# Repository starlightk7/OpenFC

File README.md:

# OpenFC

## Introduction

This repository contains OSHW Reproduction Parts related to the Famicom (FC) game console under the umbrella name OpenFC.

These parts are freely available under the terms of the [CERN-OHL-S](https://github.com/starlightk7/OpenFC/blob/main/LICENSE) license for you to use, study, modify, or sell. The source files are provided as-is with no warranty or entitlement for support to you or any users that you sell manufactured boards to. See [LICENSE](https://github.com/starlightk7/OpenFC/blob/main/LICENSE) and [NOTICE](https://github.com/starlightk7/OpenFC/blob/main/NOTICE) for details. Please carefully read these files to understand your obligations if you choose to distribute this project or modifications of it.

## Sample Build

<div></div>

## Usage

Suggested usage for the documents and boards in this repository:

* Studying the hardware and learning about it's function
* Aiding repairs and failure diagnostics through the created [schematics](https://starlightk7.github.io/OpenFC/#/schematic) and boardviews
* Repairing broken consoles via replacement, reproduction boards and tested replacement [BOMs](https://starlightk7.github.io/OpenFC/#/bom).
* Building a customized console as a DIY project, for hobby or educational purposes.

## Documentation

Please read the [documentation](https://starlightk7.github.io/OpenFC/) carefully before using the project.

You can also watch an HVC install video from [1upRestorations (English)](https://youtu.be/V8x1_Q33Uts)

## Getting a Board

The project officially distributes boards from [Japan (inexpensive international shipping available)](https://ko-fi.com/starlightk7/shop), the [US](https://1uprestorations.com/collections/console-mod-parts/) and the [UK](https://www.retroupgrades.co.uk/). If you just wish to simply obtain a board for yourself, it will often be cheaper than ordering from the fab directly.

***Support is offered to those who purchased a board from a vendor listed below. No support is provided for fabricating these files on your own. If you choose that route, you should understand what you are doing and are responsible for ensuring it is done right. I am not responsible for any defects that may arise from improperly manufacturing these files, or for defects arising from modifications made by you or your PCB fab during manufacturing. If you produce these boards for sale without becoming an authorized distributor, you are responsible for any and all customer support related to the product as well as your compliance with the project's license***. 

If you have any questions about this, feel free to contact with questions. If you are interested in becoming an authorized distributor for your region, and thus gaining support for your users, please contact me via Discord or Twitter.

The ultimate goal of this project is to eventually document and reproduce all models, but it will take quite some time. If you believe in the long term goal, consider subscribing on Ko-Fi; labor aside, donor boards to research, prototypes, and parts are all expensive, and those funds will help offset those costs to complete more boards.

Feel free to come chat with us on Discord: 

All boards in this project are ~40 years old at the time of writing. All relevant patents worldwide have long expired. This project is not affiliated with or endorsed by the big N.

## Commissions

I do not have time to build commissions on a regular basis, however, there are members of the retro community whom offer this service.

| US/Canada |
|-----------|
| [1upRestorations (United States)'](https://1uprestorations.com/) |

## Disclaimer

**WARNING:** Doing a full build is an advanced project. Please carefully read the documentation and required skills and experience before purchasing or ordering a board. Purchasing boards and parts does not guarantee that you can be successful in doing a build. Significant experience in soldering and desoldering, along with a variety of tools are necessary. Your first build will likely not work on its first boot. Patience, analysis, and debugging will likely be necessary to bring the unit online. Order at your own risk. The author provides no guarantee of your success, and also cannot guarantee that any given vendor can fabricate these boards correctly. If you are ordering boards, please consult with your target vendor before ordering if you wish to order a board.

## Parts Index

### Motherboards

| Part Number | Description | Region | Status| Japan | United States | United Kingdom |
|-------------|-------------|----------------------|-------|-------|---------------|----------------|
| HVC-CPU-01 | AV Famicom / New Famicom | NTSC-J | Need Donor  | N/A | N/A | N/A |
| HVC-CPU-02 | AV Famicom / New Famicom | NTSC-J | Need Donor  | N/A | N/A | N/A |
| HVC-CPU-03 | AV Famicom / New Famicom | NTSC-J | Planned     | N/A | N/A | N/A |
| HVC-CPU-04 | AV Famicom / New Famicom | NTSC-J | Planned     | N/A | N/A | N/A |
| HVC-CPU-05 | AV Famicom / New Famicom | NTSC-J | Planned     | N/A | N/A | N/A |
| HVC-CPU-06 | AV Famicom / New Famicom | NTSC-J | Planned     | N/A | N/A | N/A |
| HVC-CPU-07 (1984) | The most common HVC motherboard. Most often comes with Rev. E chips. | NTSC-J | Released | [Ko-Fi (Direct)](https://ko-fi.com/starlightk7/shop), [eBay (Direct)](https://www.ebay.com/usr/starlightk7), [Etsy (Direct)](https://starlightretro.etsy.com) | [1upRestorations](https://1uprestorations.com/collections/console-mod-parts) | [RetroUpgrades](https://www.retroupgrades.co.uk/product/opensfc-shvc-bundle) |
| HVC-CPU-GPM-01 | Redesign that worked on lowering EMI for VCCI compliance | NTSC-J | Planned | N/A | N/A | N/A |
| HVC-CPU-GPM-02 | Redesign that worked on lowering EMI for VCCI compliance | NTSC-J | Planned | N/A | N/A | N/A |
| HVCN-CPU-01 | AV Famicom / New Famicom | NTSC-J | Need Donor  | N/A | N/A | N/A |
| HVCN-CPU-02 | AV Famicom / New Famicom | NTSC-J | In Progress | N/A | N/A | N/A |

### Power AV

| Part Number | Description | Region | Status| Japan | United States | United Kingdom |
|-------------|-------------|----------------------|-------|-------|---------------|----------------|
| KP-782 | Early Type Original Power / RF Board | NTSC-J | Planned | N/A | N/A | N/A |
| KP-917 | Late Type Original Power / RF Board | NTSC-J | In Testing | N/A | N/A | N/A |
| OFC-PWRAV-01 | Original Design. Backport of SFC-style Power/Audio circuit w/ THS7314 for Composite Video. | NTSC-J | Released | [Ko-Fi (Direct)](https://ko-fi.com/starlightk7/shop), [eBay (Direct)](https://www.ebay.com/usr/starlightk7), [Etsy (Direct)](https://starlightretro.etsy.com) | [1upRestorations](https://1uprestorations.com/collections/console-mod-parts) | [RetroUpgrades](https://www.retroupgrades.co.uk/product/opensfc-shvc-bundle) |

### Controllers

| Part Number | Description | Region | Status| Japan | United States | United Kingdom |
|-------------|-------------|----------------------|-------|-------|---------------|----------------|
| 56.8231A | Found in Early Circle Button Controllers Pre-NES Launch | NTSC-J | Planned | N/A | N/A | N/A |
| 56.8231B | Found in Most Circle Buttton Controllers. Official NES Support | NTSC-J / NTSC-U | Released | [Ko-Fi (Direct)](https://ko-fi.com/starlightk7/shop), [eBay (Direct)](https://www.ebay.com/usr/starlightk7), [Etsy (Direct)](https://starlightretro.etsy.com) | [1upRestorations](https://1uprestorations.com/collections/console-mod-parts) | [RetroUpgrades](https://www.retroupgrades.co.uk/product/opensfc-shvc-bundle) |
| 56.8232A  | Circle Button Player 2 Controller | NTSC-J | Released | [Ko-Fi (Direct)](https://ko-fi.com/starlightk7/shop), [eBay(Direct)](https://www.ebay.com/usr/starlightk7) | [1upRestorations](https://1uprestorations.com/collections/console-mod-parts) | [RetroUpgrades](https://www.retroupgrades.co.uk/) |

### Cartridges

There are none currently in progress, but they are planned for future.

### Accessories

There are none currently in progress, but they planned for future.

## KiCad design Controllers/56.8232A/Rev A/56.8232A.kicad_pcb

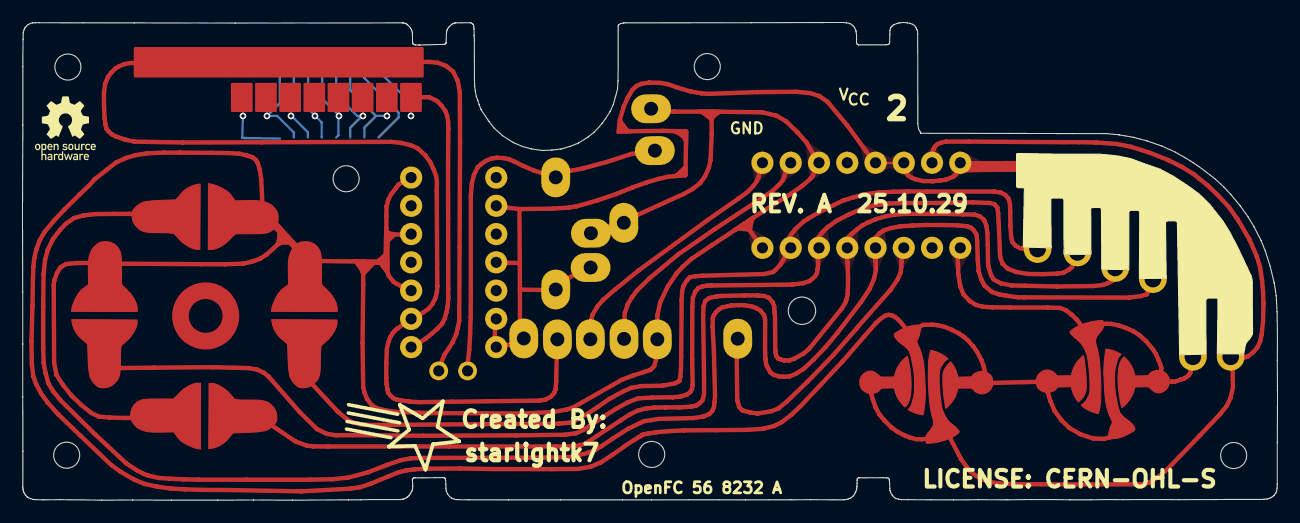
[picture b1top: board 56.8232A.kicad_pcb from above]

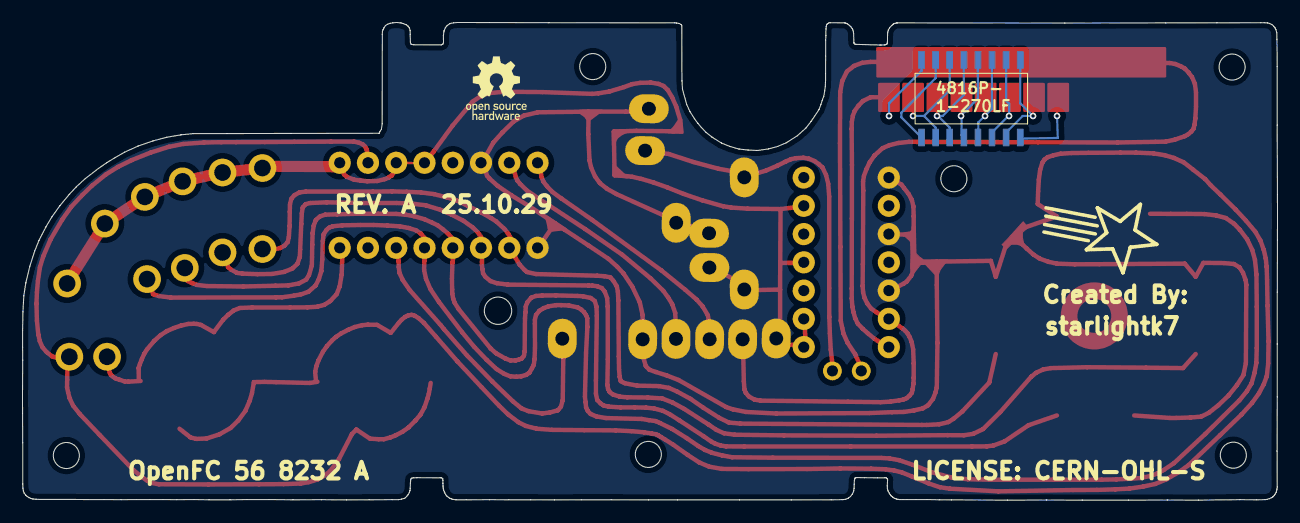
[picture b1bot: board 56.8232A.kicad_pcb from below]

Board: 2 copper layers, 113.0 x 43.0 mm, 23 parts (4 on the bottom side), 21 nets.

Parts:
C1: 0.33uf; C_THT_Small
IC1: IC4021
IC2: MIC_IC
J1, J2, J3, J4, J5, J7, J8, J9, J11, J12, J13: +5V; P1_Wire
R1: 2.2k; R_THT_Alt_Long
RN1: 40k x6; P2_CarbonTraces
RN2: 27ohm x8 SOIC; R_Array_08_SOIC16
S1: LEFT; P1_DPad
S3: UP; P1_DPad
S4: RIGHT; P1_DPad
S5: DOWN; P1_DPad
S9: B; P1_AB
S10: A; P1_AB

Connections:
GND: IC1.8 (GND), IC1.11 (GND), IC2.3 (I2), IC2.5 (I3), IC2.7 (VSS), J4.1, J8.1, J9.1, J12.1, S1.2 (Out), S3.2 (Out), S4.2 (Out), S5.2 (Out), S9.2 (Out), S10.2 (Out)
unnamed: IC1.1 (A), RN1.10, S10.1 (In)
unnamed: IC1.15 (B), RN1.12, S9.1 (In)
unnamed: IC1.10 (CLK), J3.1
unnamed: IC1.3 (Data), J13.1
unnamed: IC1.5 (Down), RN1.6, S5.1 (In)
unnamed: IC1.9 (Latch), J2.1
unnamed: IC1.6 (Left), RN1.4, S1.1 (In)
unnamed: IC1.7 (Right), RN1.2, S4.1 (In)
unnamed: IC1.4 (Up), RN1.8, S3.1 (In)
unnamed: IC2.1 (I1), RN2.16 (R1.2)
unnamed: C1.2, IC2.2 (O1), J1.1
unnamed: C1.1, J11.1, R1.1
unnamed: RN2.1 (R1.1), RN2.15 (R2.2)
unnamed: RN2.2 (R2.1), RN2.14 (R3.2)
unnamed: RN2.3 (R3.1), RN2.13 (R4.2)
unnamed: RN2.4 (R4.1), RN2.12 (R5.2)
unnamed: RN2.5 (R5.1), RN2.11 (R6.2)
unnamed: RN2.6 (R6.1), RN2.10 (R7.2)
unnamed: RN2.7 (R7.1), RN2.9 (R8.2)
VCC: IC1.13 (Start), IC1.14 (Sel.), IC1.16 (5V), IC2.9 (I4), IC2.11 (I5), IC2.13 (I6), IC2.14 (VDD), J5.1, J7.1, R1.2, RN1.1, RN1.3, RN1.5, RN1.7, RN1.9, RN1.11

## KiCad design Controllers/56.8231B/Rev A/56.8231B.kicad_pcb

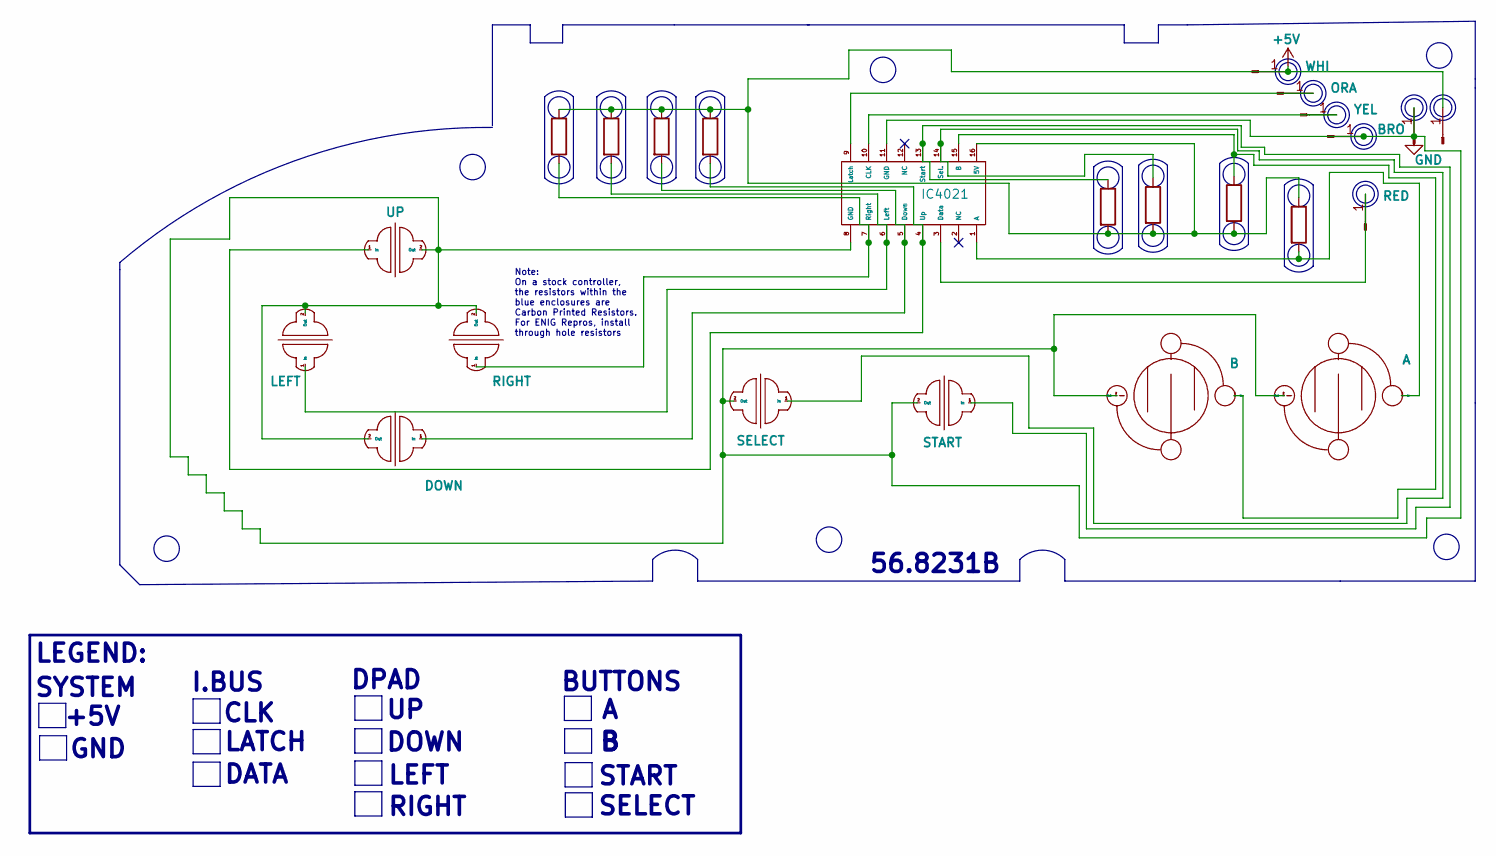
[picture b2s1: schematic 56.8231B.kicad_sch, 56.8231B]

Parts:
IC1: IC4021
J1: ORA; P1_Wire
J2: WHI; P1_Wire
J3: YEL; P1_Wire
J4: BRO; P1_Wire
J5: +5V; P1_Wire
J6: GND; P1_Wire
J7: RED; P1_Wire
R1, R2, R3, R4, R5, R6, R7, R8: R; CarbonResistor
S1: LEFT; P1_DPad
S2: SELECT; P1_SelectStart
S3: UP; P1_DPad
S4: RIGHT; P1_DPad
S5: DOWN; P1_DPad
S6: START; P1_SelectStart
S9: B; P1_AB
S10: A; P1_AB

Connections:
+5V: IC1.16 (5V), J2.1, J5.1, R1.1, R2.1, R3.1, R4.1, R5.2, R6.2, R7.2, R8.1
GND: IC1.8 (GND), IC1.11 (GND), J4.1, J6.1, S1.2 (Out), S2.2 (Out), S3.2 (Out), S4.2 (Out), S5.2 (Out), S6.2 (Out), S9.2 (Out), S10.2 (Out)
unnamed: IC1.1 (A), R8.2, S10.1 (In)
unnamed: IC1.15 (B), R7.1, S9.1 (In)
unnamed: IC1.10 (CLK), J3.1
unnamed: IC1.3 (Data), J7.1
unnamed: IC1.5 (Down), R3.2, S5.1 (In)
unnamed: IC1.9 (Latch), J1.1
unnamed: IC1.6 (Left), R2.2, S1.1 (In)
unnamed: IC1.7 (Right), R1.2, S4.1 (In)
unnamed: IC1.14 (Sel.), R6.1, S2.1 (In)
unnamed: IC1.13 (Start), R5.1, S6.1 (In)
unnamed: IC1.4 (Up), R4.2, S3.1 (In)

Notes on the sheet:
BUTTONS
START
LEFT
DOWN
Note: On a stock controller, the resistors within the blue enclosures are Carbon Printed Resistors. For ENIG Repros, install through hole resistors
DATA
56.8231B
LATCH
SELECT
DPAD
LEGEND:
+5V
SYSTEM
CLK
GND
RIGHT
I.BUS

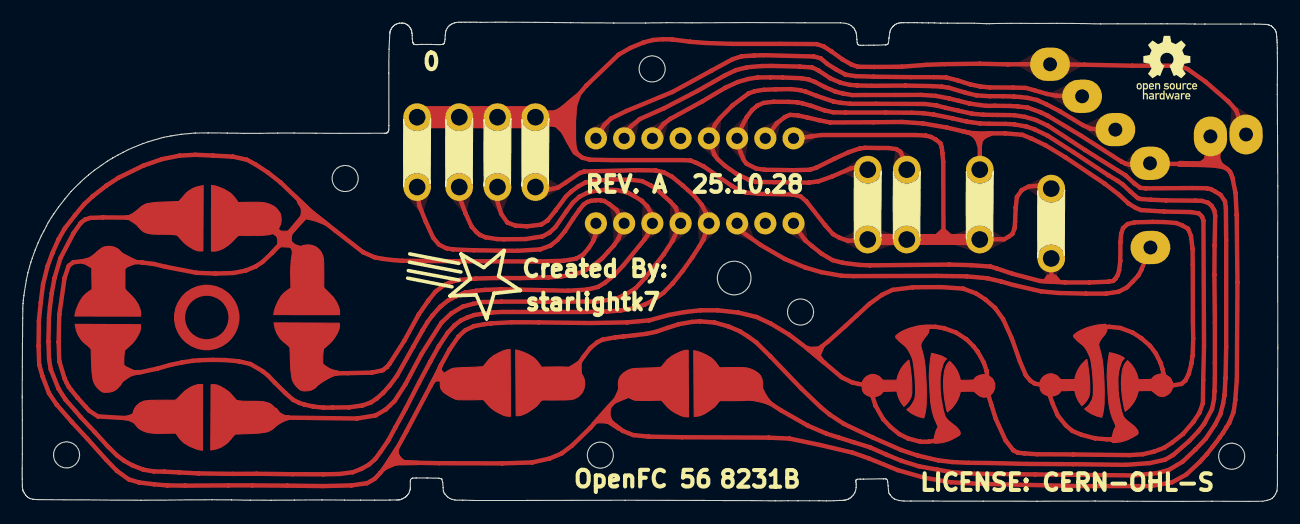
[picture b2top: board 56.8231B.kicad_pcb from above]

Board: 2 copper layers, 113.2 x 43.2 mm, 24 parts (1 on the bottom side), 13 nets.

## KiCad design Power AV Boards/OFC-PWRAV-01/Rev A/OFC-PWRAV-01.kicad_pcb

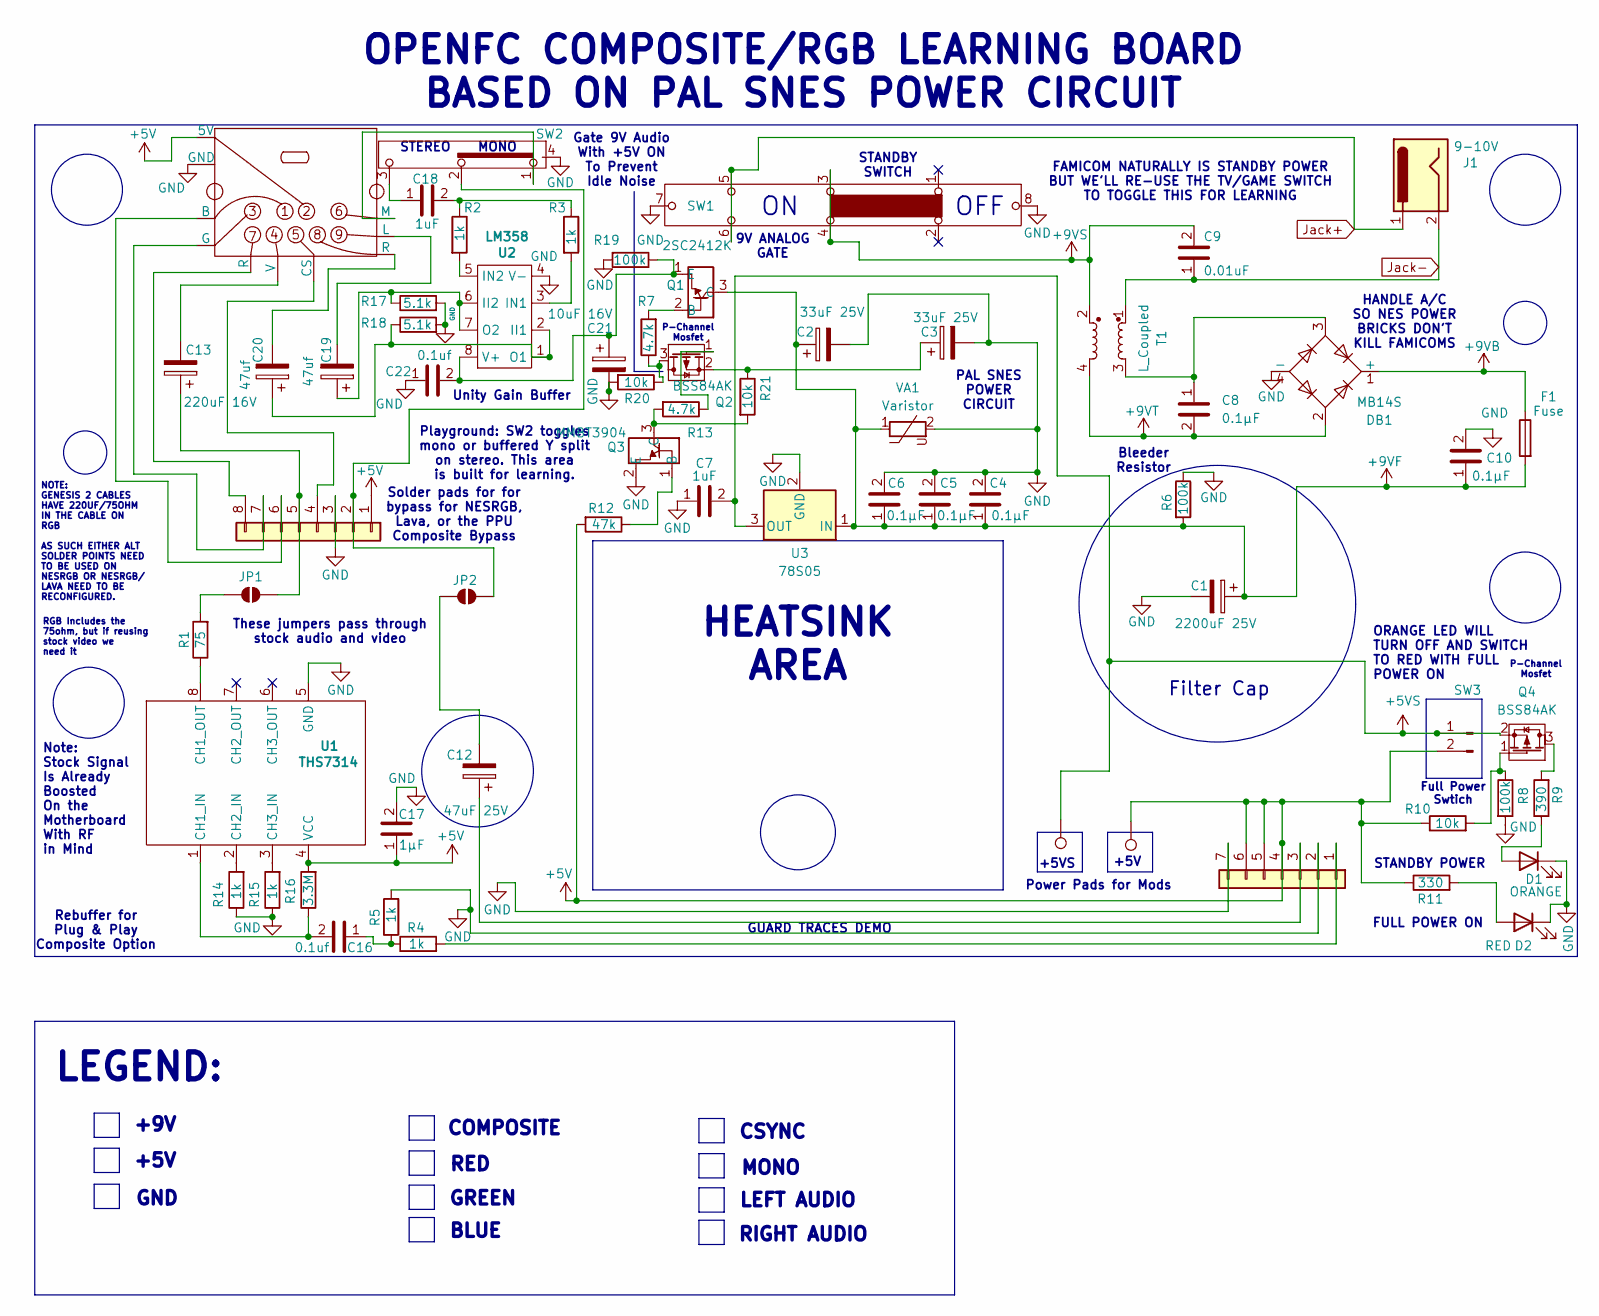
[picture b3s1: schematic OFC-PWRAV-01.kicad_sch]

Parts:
C1: 2200uF 25V; SFC_FilterCap
C2, C3: 33uF 25V; CP_Elec_6.3x3
C4, C5, C6, C8, C10: 0.1µF; SFC_SMD_0805
C7, C18: 1uF; SFC_SMD_0805
C9: 0.01uF; SFC_SMD_0805
C12: 47uF 25V; SFC_THT_Cap
C13: 220uF 16V; SFC_THT_Cap_S
C16, C22: 0.1uf; SFC_SMD_0805
C17: 1µF; SFC_SMD_0805
C19, C20: 47uf; SFC_THT_Cap
C21: 10uF 16V; SFC_SMD_CAP_S
D1: ORANGE; SFC_SMD_0805
D2: RED; SFC_SMD_0805
DB1: MB14S; Diode_Bridge_Vishay_MBLS
F1: Fuse; SFC_FUSE
J1: 9-10V; SFC_DCJack
J2, J3: Conn_01x07; HVC_Ribbon
J4: MD-90SM; DIN_9P; PARTREV 02/18/2022
JP1, JP2: SolderJumper_2_Open; SolderJumper-2_P1.3mm_Open_Pad1.0x1.5mm
Q1: 2SC2412K; Q_SOT
Q2, Q4: BSS84AK; Q_SOT_23
Q3: MMBT3904; Q_SOT_23
R1: 75; SFC_SMD_0805
R2, R3, R4, R5, R14, R15: 1k; SFC_SMD_0805
R6, R8, R19: 100k; SFC_SMD_0805
R7, R13: 4.7k; SFC_SMD_0805
R9: 390; SFC_SMD_0805
R10, R20, R21: 10k; SFC_SMD_0805
R11: 330; SFC_SMD_0805
R12: 47k; SFC_SMD_0805
R16: 3.3M; SFC_SMD_0805
R17, R18: 5.1k; SFC_SMD_0805
SW1: SW_TV_Game
SW2: SW_Channel
SW3: Conn_01x02_Pin; SFC_PowerSwitchConnector
T1: L_Coupled; SFC_T1
TP1, TP2: TestPoint; TestPoint_Pad_1.0x1.0mm
U1: THS7314; THS7134
U2: LM358; OpAmp
U3: 78S05; 7805_Heatsink
VA1: Varistor; SFC_SMD_Varistor

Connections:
+5V: C17.1, J2.4, J2.5, J2.6, J3.1 (+5VA), J4.2 (5V), R10.1, R11.1, R12.2, R16.2, SW3.2, TP2.1, U1.4 (VCC)
+5VS: C7.2, Q4.2 (S), SW3.1, TP1.1, U3.3 (OUT)
+9VB: DB1.1 (+), F1.1
+9VF: C1.1, C2.1, C4.1, C5.1, C6.1, C10.1, F1.2, Q1.3 (C), R6.2, U3.1 (IN), VA1.1
+9VS: C9.2, SW1.3, SW1.4, T1.2
+9VT: C8.2, DB1.2, T1.4
GND: C1.2, C2.2, C3.2, C4.2, C5.2, C6.2, C7.1, C10.2, C17.2, C21.2, C22.1, D1.1 (K), D2.1 (K), DB1.4 (-), J2.2, J2.7, J3.3 (AGND), J4.10 (GND), Q3.2 (E), R5.2, R6.1, R8.2, R14.1, R15.1, R17.2, R18.2, R19.2, R20.2, SW1.7, SW1.8, SW2.4, U1.5 (GND), U2.4 (V-), U3.2 (GND), VA1.2
Jack+: J1.1, SW1.5, SW1.6
Jack-: C9.1, J1.2, T1.1
unnamed: C8.1, DB1.3, T1.3
unnamed: C16.1, R4.1, R5.1
unnamed: C18.1, SW2.3
unnamed: C18.2, R2.1, R3.1
unnamed: C20.2, J4.8 (R)
unnamed: D1.2 (A), R9.1
unnamed: D2.2 (A), R11.2
unnamed: J2.1, R4.2
unnamed: C12.1, J2.3
unnamed: J3.2 (A), JP2.2 (B), SW2.2
unnamed: J3.4 (CS), J4.5 (CS)
unnamed: J3.7 (G), J4.3 (G)
unnamed: J3.8 (R), J4.7 (R)
unnamed: J3.6 (B), J4.1 (B)
unnamed: C19.2, J4.9 (L)
unnamed: J4.6 (M), SW2.1
unnamed: C13.2, J4.4 (V)
unnamed: JP1.1 (A), R1.2
unnamed: C13.1, J3.5 (B), JP1.2 (B)
unnamed: C12.2, JP2.1 (A)
unnamed: Q1.2 (B), R7.2
unnamed: C21.1, C22.2, Q1.1 (E), R19.1, U2.8 (V+)
unnamed: Q2.3 (D), R7.1, R20.1
unnamed: Q2.1 (G), R13.1
unnamed: C3.1, Q2.2 (S), R21.1
unnamed: Q3.1 (B), R12.1
unnamed: Q3.3 (C), R13.2, R21.2
unnamed: Q4.3 (D), R9.2
unnamed: Q4.1 (G), R8.1, R10.2
unnamed: C16.2, R16.1, U1.1 (CH1_IN)
unnamed: R1.1, U1.8 (CH1_OUT)
unnamed: R14.2, U1.2 (CH2_IN)
unnamed: R15.2, U1.3 (CH3_IN)
unnamed: C20.1, R18.1, U2.1 (O1), U2.2 (II1)
unnamed: C19.1, R17.1, U2.6 (II2), U2.7 (O2)
unnamed: R3.2, U2.3 (IN1)
unnamed: R2.2, U2.5 (IN2)

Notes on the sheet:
STEREO
STANDBY POWER
Solder pads for for bypass for NESRGB, Lava, or the PPU Composite Bypass
RIGHT AUDIO
9V ANALOG GATE
HANDLE A/C SO NES POWER BRICKS DON'T KILL FAMICOMS
+5V
Filter Cap
RGB Includes the 75ohm, but if reusing stock video we need it
P-Channel Mosfet
ORANGE LED WILL TURN OFF AND SWITCH TO RED WITH FULL POWER ON
RED
MONO
LEFT AUDIO
Unity Gain Buffer
PAL SNES POWER CIRCUIT
OFF
GUARD TRACES DEMO
FAMICOM NATURALLY IS STANDBY POWER BUT WE'LL RE-USE THE TV/GAME SWITCH TO TOGGLE THIS FOR LEARNING
Gate 9V Audio With +5V ON To Prevent Idle Noise
+5VS
NOTE: GENESIS 2 CABLES HAVE 220UF/75OHM IN THE CABLE ON RGB AS SUCH EITHER ALT SOLDER POINTS NEED TO BE USED ON NESRGB OR NESRGB/ LAVA NEED TO BE RECONFIGURED.
Note: Stock Signal Is Already Boosted On the Motherboard With RF in Mind
Playground: SW2 toggles mono or buffered Y split on stereo. This area is built for learning.
Rebuffer for Plug & Play Composite Option
COMPOSITE
CSYNC
Bleeder Resistor
HEATSINK AREA
Power Pads for Mods
These jumpers pass through stock audio and video
Full Power Swtich
LEGEND:
GND
+9V
STANDBY SWITCH
OPENFC COMPOSITE/RGB LEARNING BOARD BASED ON PAL SNES POWER CIRCUIT
GREEN
BLUE
FULL POWER ON

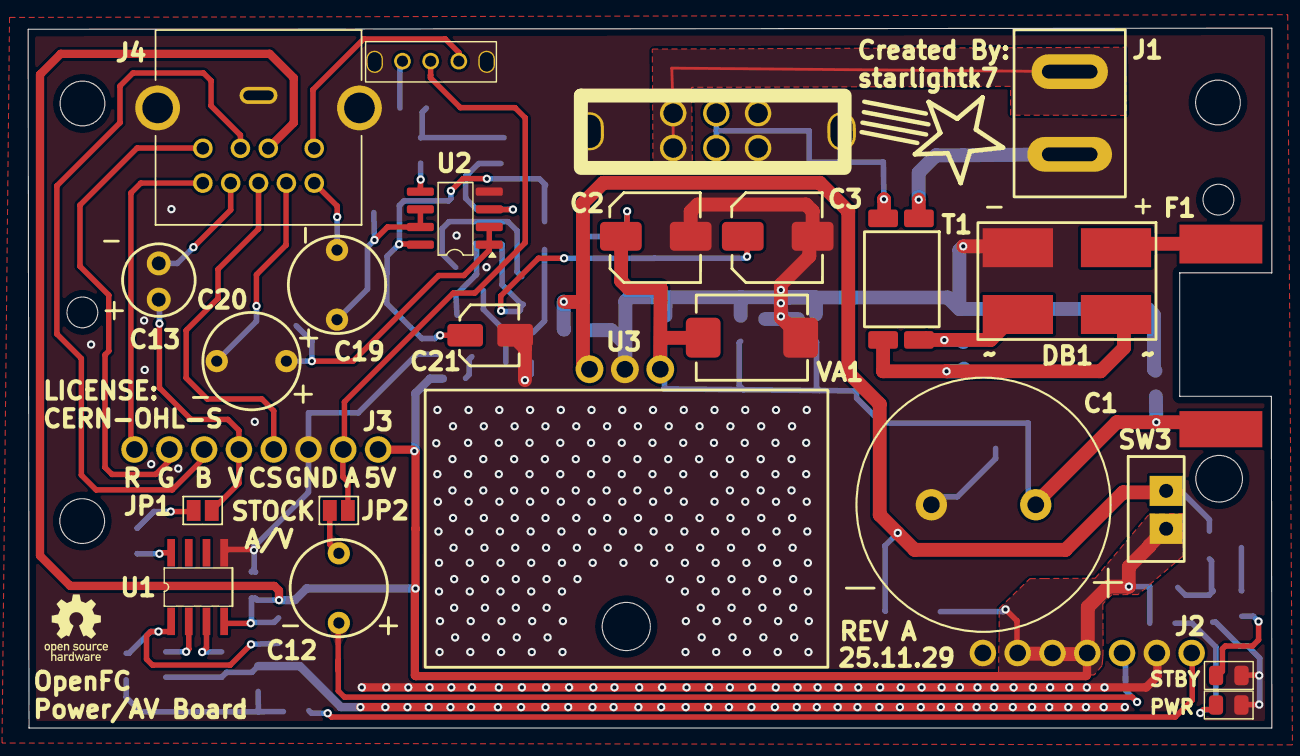
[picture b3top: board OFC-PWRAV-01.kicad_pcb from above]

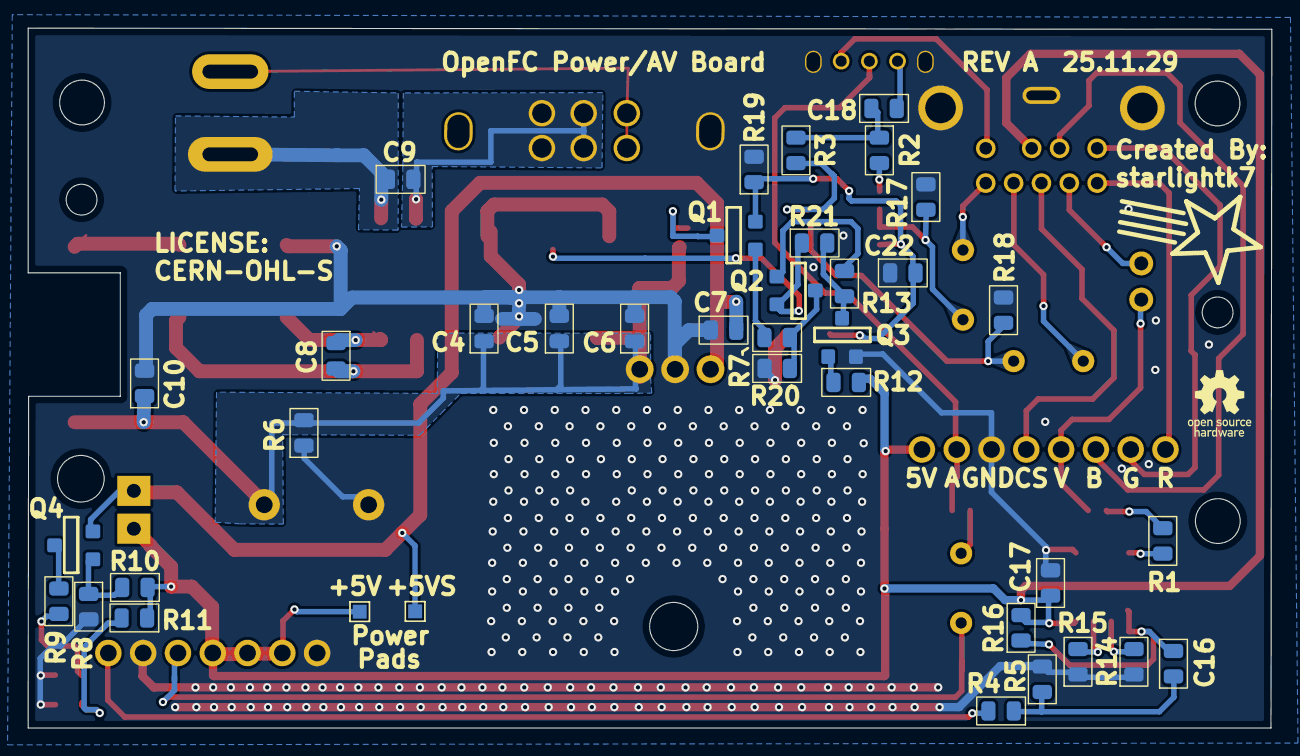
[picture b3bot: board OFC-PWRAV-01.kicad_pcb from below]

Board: 4 copper layers, 89.3 x 50.3 mm, 64 parts (38 on the bottom side), 46 nets.

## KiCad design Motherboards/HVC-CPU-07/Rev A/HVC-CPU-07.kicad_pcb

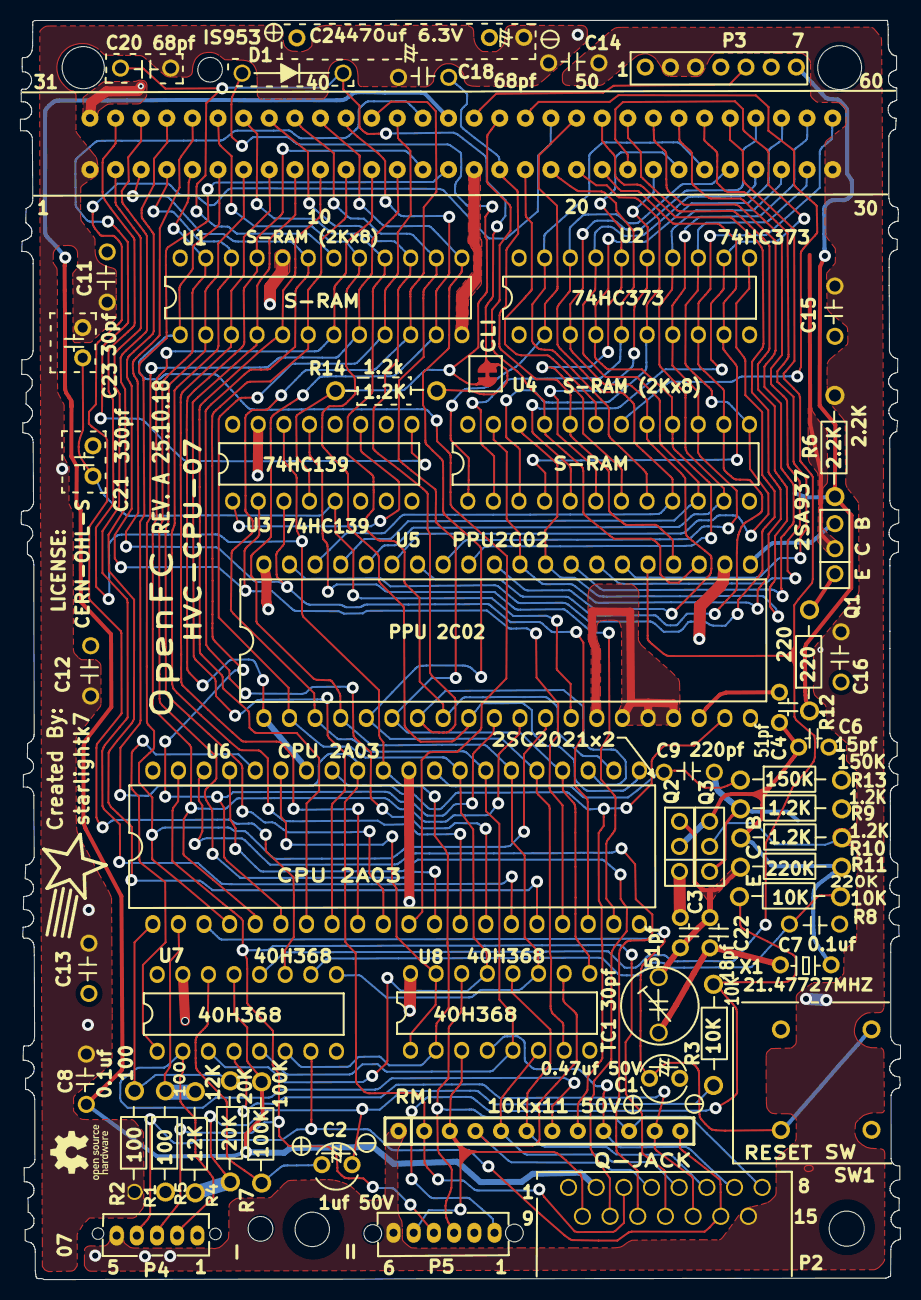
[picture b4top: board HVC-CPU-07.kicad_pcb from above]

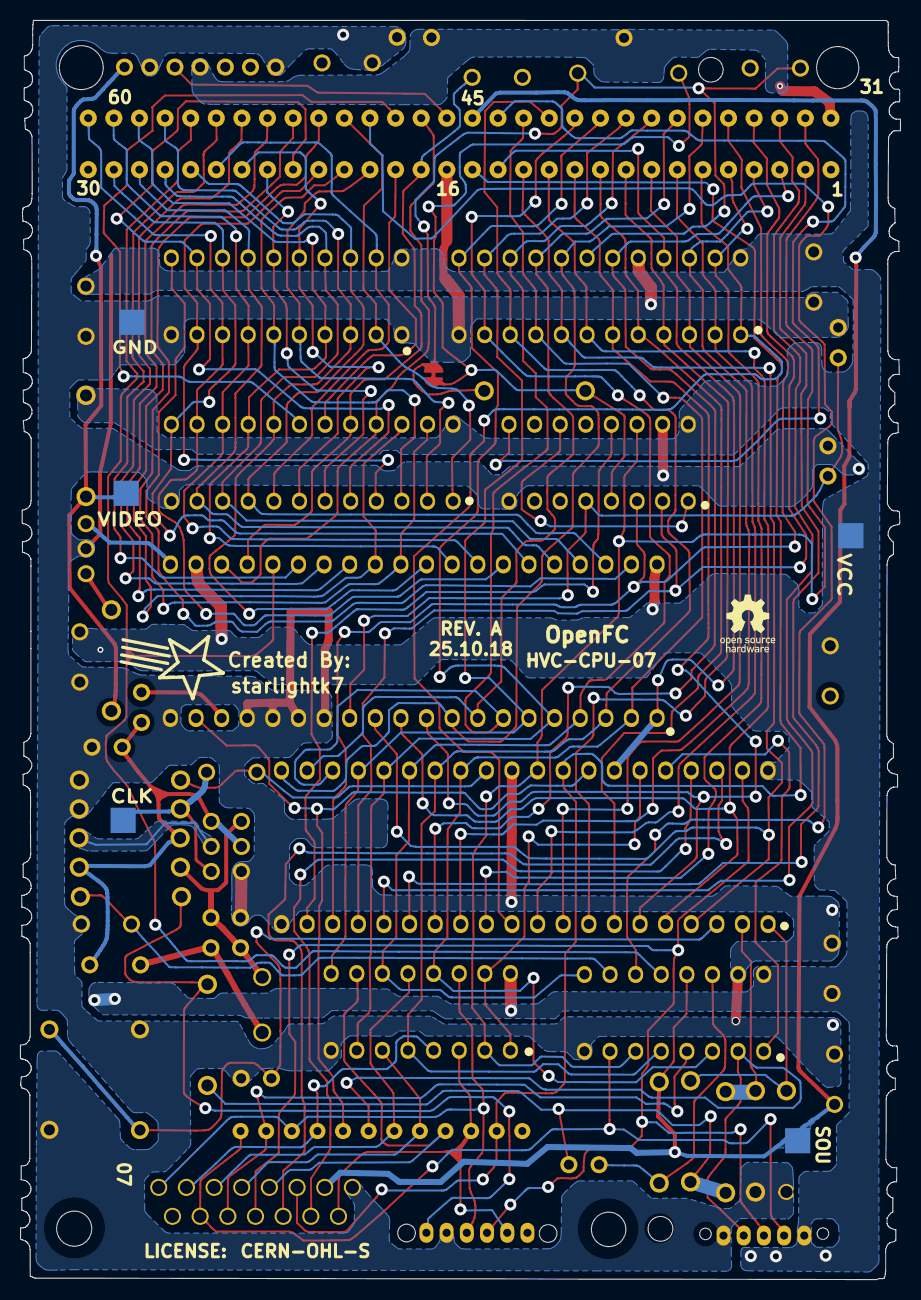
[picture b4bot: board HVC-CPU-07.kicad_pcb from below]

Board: 4 copper layers, 87.3 x 124.9 mm, 60 parts (5 on the bottom side), 95 nets.

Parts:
C1: 0.47uf 50V; C_Electrolytic
C2: 1uf 50V; C_Electrolytic_Small
C3, C4: 51pf; C_THT_Small
C6: 15pf; C_THT_Small
C7, C8, C11, C12, C13, C14, C15, C16: 0.1uf; C_THT
C9: 220pf; C_THT
C18, C20: 68pf; C_THT
C21: 330pf; C_THT_Small
C22: 18pf; C_THT_Small
C23: 30pf; C_THT_Small
C24: 470uf 6.3V; C_Axial
D1: Diode_THT
P1: 60PinCartSlot
P2: Q-JACK; D-JACK
P3: Conn_01x07; P3_PowerRibbon
P4: Conn_01x05; P4_Controller1
P5: Conn_01x06; P5_Controller2
Q1: 2SA937; Q_THT
Q2, Q3: 25C2021; Q_THT
R1, R2: 100; R_THT
R3, R8: 10K; R_THT
R4: 20K; R_THT
R5: 12K; R_THT
R6: 2.2K; R_THT
R7: 100K; R_THT
R9, R10, R14: 1.2K; R_THT
R11: 220K; R_THT
R12: 220; R_THT
R13: 150K; R_THT
RM1: 10Kx11 50V; R_Array_SIP12
SW1: RESET SW; RESET_SW
TC1: 30pf; TC1
TP1, TP2, TP3, TP4, TP5: TestPoint_Pad_2.5x2.5mm
U1, U4: S-RAM (2Kx8); S-RAM_2Kx8
U2: 74HC373
U3: 74HC139; 74HC139_40H368
U5: PPU 2C02; CPU_PPU
U6: CPU 2A03; CPU_PPU
U7, U8: 40H368; 74HC139_40H368
X1: 21.47727MHZ; Crystal

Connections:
1G: U3.1 (1G), U3.11 (2Y1)
A.IN: C8.1, P1.45 (A.IN), P2.2, R7.1, TP5.1, U7.13 (2Y2)
AD1: R2.1, R4.1, U6.1 (AD1)
AD2: R1.1, R5.1, U6.2 (AD2)
ALE: U2.11 (LE), U5.39 (ALE)
C2: C2.2, R3.1, R4.2, R5.2
C3: C3.1, C22.2, Q2.3, R11.2, TC1.1
C.A0: P1.13 (C.A0), U1.8 (A0), U5.12 (C.A0), U6.4 (A0)
C.A1: P1.12 (C.A1), U1.7 (A1), U5.11 (C.A1), U6.5 (A1)
C.A2: P1.11 (C.A2), U1.6 (A2), U5.10 (C.A2), U6.6 (A2)
C.A4: P1.9 (C.A4), U1.4 (A4), U6.8 (A4)
C.A5: P1.8 (C.A5), U1.3 (A5), U6.9 (A5)
C.A6: P1.7 (C.A6), U1.2 (A6), U6.10 (A6)
C.A7: P1.6 (C.A7), U1.1 (A7), U6.11 (A7)
C.A8: P1.5 (C.A8), U1.23 (A8), U6.12 (A8)
C.A9: P1.4 (C.A9), U1.22 (A9), U6.13 (A9)
C.A10: P1.3 (C.A10), U1.19 (A10), U6.14 (A10)
C.A11: P1.2 (C.A11), U6.15 (A11)
C.A12: P1.33 (C.A12), U6.16 (A12)
C.A13: P1.34 (C.A13), U3.2 (1A), U6.17 (A13)
C.A14: P1.35 (C.A14), U3.3 (1B), U6.18 (A14)
C.A15: U3.13 (2B), U6.19 (A15)
CD0: P1.43 (C.D0), U1.9 (D0), U5.2 (C.D0), U6.28 (D0), U7.3 (1Y1), U8.13 (2Y2)
CD1: P1.42 (C.D1), U1.10 (D1), U5.3 (C.D1), U6.27 (D1), U7.5 (1Y2), U8.5 (1Y2)
CD2: P1.41 (C.D2), U1.11 (D2), U5.4 (C.D2), U6.26 (D2), U7.9 (1Y4), U8.11 (2Y1)
CD3: P1.40 (C.D3), U1.13 (D3), U5.5 (C.D3), U6.25 (D3), U8.7 (1Y3)
CD4: P1.39 (C.D4), U1.14 (D4), U5.6 (C.D4), U6.24 (D4), U8.9 (1Y4)
CD5: P1.38 (C.D5), U1.15 (D5), U5.7 (C.D5), U6.23 (D5)
CD6: P1.37 (C.D6), U1.16 (D6), U5.8 (C.D6), U6.22 (D6)
CD7: P1.36 (C.D7), U1.17 (D7), U5.9 (C.D7), U6.21 (D7)
CLK: C9.1, R13.2, U6.29 (CLK)
D1: C20.2, D1.1 (K), D1.2 (A), R14.1, R14.2, U1.18 (/CE), U3.4 (1Y0)
GND: C1.2, C3.2, C6.1, C7.1, C8.2, C11.1, C12.1, C13.2, C14.1, C15.1, C16.1, C18.1, C20.1, C21.1, C23.1, C24.2, P1.1 (GND), P1.16 (GND), P2.1, P3.1, P3.6, P4.1, P5.2, Q1.2, Q2.1, R1.2, R2.2, R9.1, R13.1, SW1.1, SW1.3, TP1.1, U1.12 (GND), U1.20 (/OE), U2.1 (/OE), U2.10 (GND), U3.8 (GND), U3.15 (2G), U4.12 (GND), U5.14 (EXT0), U5.15 (EXT1), U5.16 (EXT2), U5.17 (EXT3), U5.20 (GND), U6.20 (GND), U6.30 (TST), U7.8 (GND), U7.15 (/2G), U8.8 (GND)
IRQ: P1.15 (/IRQ), P2.3, RM1.2, U6.32 (/IRQ)
M2: P1.32 (M2), U3.14 (2A), U6.31 (M2), U7.6 (1A3), U8.2 (1A1)
NMI: RM1.8, U5.19 (/INT), U6.33 (/NMI)
unnamed: C22.1, TC1.2, X1.1
unnamed: P1.46 (A.OUT), P3.5
unnamed: P1.10 (C.A3), U1.5 (A3), U6.7 (A3)
unnamed: P1.47 (P.RW), U4.21 (/WE), U5.23 (/WR)
unnamed: P1.18 (R.A10), U4.19 (A10)
unnamed: Q1.1, R12.1
unnamed: C4.2, U5.18 (CLK)
OE1: U6.36 (/OE1), U7.1 (/1G)
OE2: U6.35 (/OE2), U8.1 (/1G), U8.15 (/2G)
OUT0: P2.12, P4.3, P5.4, U6.39 (OUT0)
OUT1: P2.11, U6.38 (OUT1)
OUT2: P2.10, U6.37 (OUT2)
P5.5: P2.9, P5.5, RM1.3, U8.3 (1Y1)
P.A13: P1.49 (P.A13), U7.11 (2Y1)
PA0: P1.25 (P.A0), U2.19 (Q7), U4.8 (A0)
PA1: P1.24 (P.A1), U2.16 (Q6), U4.7 (A1)
PA2: P1.23 (P.A2), U2.15 (Q5), U4.6 (A2)
PA3: P1.22 (P.A3), U2.12 (Q4), U4.5 (A3)
PA4: P1.21 (P.A4), U2.9 (Q3), U4.4 (A4)
PA5: P1.20 (P.A5), U2.6 (Q2), U4.3 (A5)
PA6: P1.19 (P.A6), U2.5 (Q1), U4.2 (A6)
PA7: P1.50 (P.A7), U2.2 (Q0), U4.1 (A7)
PA8: P1.51 (P.A8), U4.23 (A8), U5.30 (P.A8)
PA9: P1.52 (P.A9), U4.22 (A9), U5.29 (P.A9)
PA10: P1.53 (P.A10), U5.28 (P.A10)
PA11: P1.54 (P.A11), U5.27 (P.A11)
PA12: P1.55 (P.A12), U5.26 (P.A12)
PD0: P1.26 (P.D0), U2.18 (D7), U4.9 (D0), U5.38 (P.AD0)
PD1: P1.27 (P.D1), U2.17 (D6), U4.10 (D1), U5.37 (P.AD1)
PD2: P1.28 (P.D2), U2.14 (D5), U4.11 (D2), U5.36 (P.AD2)
PD3: P1.29 (P.D3), U2.13 (D4), U4.13 (D3), U5.35 (P.AD3)
PD4: P1.60 (P.D4), U2.8 (D3), U4.14 (D4), U5.34 (P.AD4)
PD5: P1.59 (P.D5), U2.7 (D2), U4.15 (D5), U5.33 (P.AD5)
PD6: P1.58 (P.D6), U2.4 (D1), U4.16 (D6), U5.32 (P.AD6)
PD7: P1.57 (P.D7), U2.3 (D0), U4.17 (D7), U5.31 (P.AD7)
R3: P5.1, R3.2, R8.2
R7: C2.1, R7.2, U7.14 (2A2)
R9: C9.2, Q3.1, R9.2, TP4.1
R.CE: P1.48 (R.CE), U4.18 (/CE)
RD: C18.2, P1.17 (/RD), U4.20 (/OE), U5.24 (/RD)
RM10: P2.8, P5.3, RM1.10, U8.14 (2A2)
RSEL: P1.44 (R.SEL), U3.9 (2Y3)
RST: C1.1, SW1.2, SW1.4, U6.3 (/RST)
R/W: P1.14 (R/W), U1.21 (/WE), U5.1 (R/W), U6.34 (R/W)
U7.2: P4.2, RM1.7, U7.2 (1A1)
U7.4: P2.13, RM1.11, U7.4 (1A2)
U7.7: P2.14, P4.4, RM1.12, U7.7 (1Y3)
U7.10: C7.2, R8.1, U7.10 (1A4)
U7.12: P1.56 (P.A13), U5.25 (P.A13), U7.12 (2A1)
U8.4: P2.7, RM1.9, U8.4 (1A2)
U8.6: P2.5, RM1.5, U8.6 (1A3)
U8.10: P2.4, RM1.4, U8.10 (1A4)
U8.12: P2.6, RM1.6, U8.12 (2A1)
VCC: C11.2, C12.2, C13.1, C14.2, C15.2, C16.2, P1.30 (VCC), P2.15, P3.2, P3.3, P4.5, P5.6, Q3.2, R6.1, R10.1, RM1.1, TP3.1, U1.24 (VCC), U2.20 (VCC), U3.16 (VCC), U4.24 (VCC), U5.22 (/RST), U5.40 (VCC), U6.40 (VCC), U7.16 (VCC), U8.16 (VCC)
VCC2: C24.1, C24.3, P1.31 (CART), P3.4
VID: P3.7, R6.2, R12.2, TP2.1
VOUT: Q1.3, U5.21 (V.OUT)
X1: C4.1, C6.2, Q2.2, Q3.3, R10.2, R11.1, X1.2
/CS: C21.2, C23.2, U3.5 (1Y1), U5.13 (/CS)

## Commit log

2026-04-24 Initial Release
2026-05-19 Fix µF vs uF label desync, regenerate iBOM for PowerAV Rev C

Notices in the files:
Controllers/56.8231B/Rev A/56.8231B.kicad_pcb:
License: CERN-OHL-S
Power AV Boards/OFC-PWRAV-01/Rev A/OFC-PWRAV-01.kicad_pcb:
(C) 2025, starlightk7, Starlight Retro
Power AV Boards/OFC-PWRAV-01/Rev C/OFC-PWRAV-01.kicad_sch:
(C) 2026, starlightk7, Starlight Retro
